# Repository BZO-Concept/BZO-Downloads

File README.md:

# BZO Concept – Downloads

Firmware, TunerStudio files, datasheets and tools for **BZO Concept** programmable ECUs and accessories.
This repository mirrors the *Téléchargements* section of [bzo-concept.fr](https://www.bzo-concept.fr/telechargements/).

Shop: [bzo-concept.fr/boutique](https://www.bzo-concept.fr/boutique/)

## ECUs (Speeduino based, STM32F4)

| Folder | Content |
|---|---|
| [Essential_v1.2](Essential_v1.2) | Firmware, TunerStudio `.ini`, base tune, datasheet |
| [Double_Eight](Double_Eight) | Firmware, TunerStudio `.ini`, base tune, datasheet (FR / EN) |
| [CoreF4_CoreF4_Boxed](CoreF4_CoreF4_Boxed) | Firmware packs `v1.2` and `2025.01.6`, `.ini`, base tunes, pinout, datasheet |
| [SmartBoard_v1.2](SmartBoard_v1.2) | Firmware (UART / USB) and integration kit: KiCad symbol, footprint, 3D model, pinout, typical application |

## Accessories

| Folder | Content |
|---|---|
| [PDU_v1.0](PDU_v1.0) | Power Distribution Unit – Arduino IDE source code, `.ini`, CAN frame sheet |
| [Mini_WideBand](Mini_WideBand) | Mini WideBand controller pinout |
| [DBW_Analog](DBW_Analog) | Analog drive-by-wire add-on datasheet |
| [Mini_OLED](Mini_OLED) | Multifunction mini OLED display datasheet |
| [Simulator](Simulator) | BZO engine simulator – source code, firmware, enclosure (FreeCAD / STEP) |
| [Bosch_55pin_Adapter](Bosch_55pin_Adapter) | Bosch 55-pin connector breakout plate (project originating from the rusEFI hardware repository) |
| [Bosch_88pin_Adapter](Bosch_88pin_Adapter) | Bosch 88-pin connector breakout plate – KiCad project and production files |
| [Speeduino_v0.4.3d](Speeduino_v0.4.3d) | BOM of the original Speeduino v0.4.3d board |

## Tools

- [BZO Programmer](Tools/BZO_Programmer) – Windows tool to flash BZO ECUs. Use it for every firmware update.
- STM32 drivers: [download from bzo-concept.fr](https://www.bzo-concept.fr/wp-content/uploads/2026/06/silent_st_drivers.zip)

## Documentation

- [Speeduino manual (EN)](https://www.bzo-concept.fr/wp-content/uploads/2025/11/Speeduino_manual.pdf)
- [Speeduino manual (FR)](https://www.bzo-concept.fr/wp-content/uploads/2025/11/Speeduino_manuel_en_fr.pdf)
- Official Speeduino project: [speeduino.com](https://speeduino.com) – [github.com/noisymime/speeduino](https://github.com/noisymime/speeduino)

## See also

Development boards and libraries: [BZO-Development](https://github.com/BZO-Concept/BZO-Development)

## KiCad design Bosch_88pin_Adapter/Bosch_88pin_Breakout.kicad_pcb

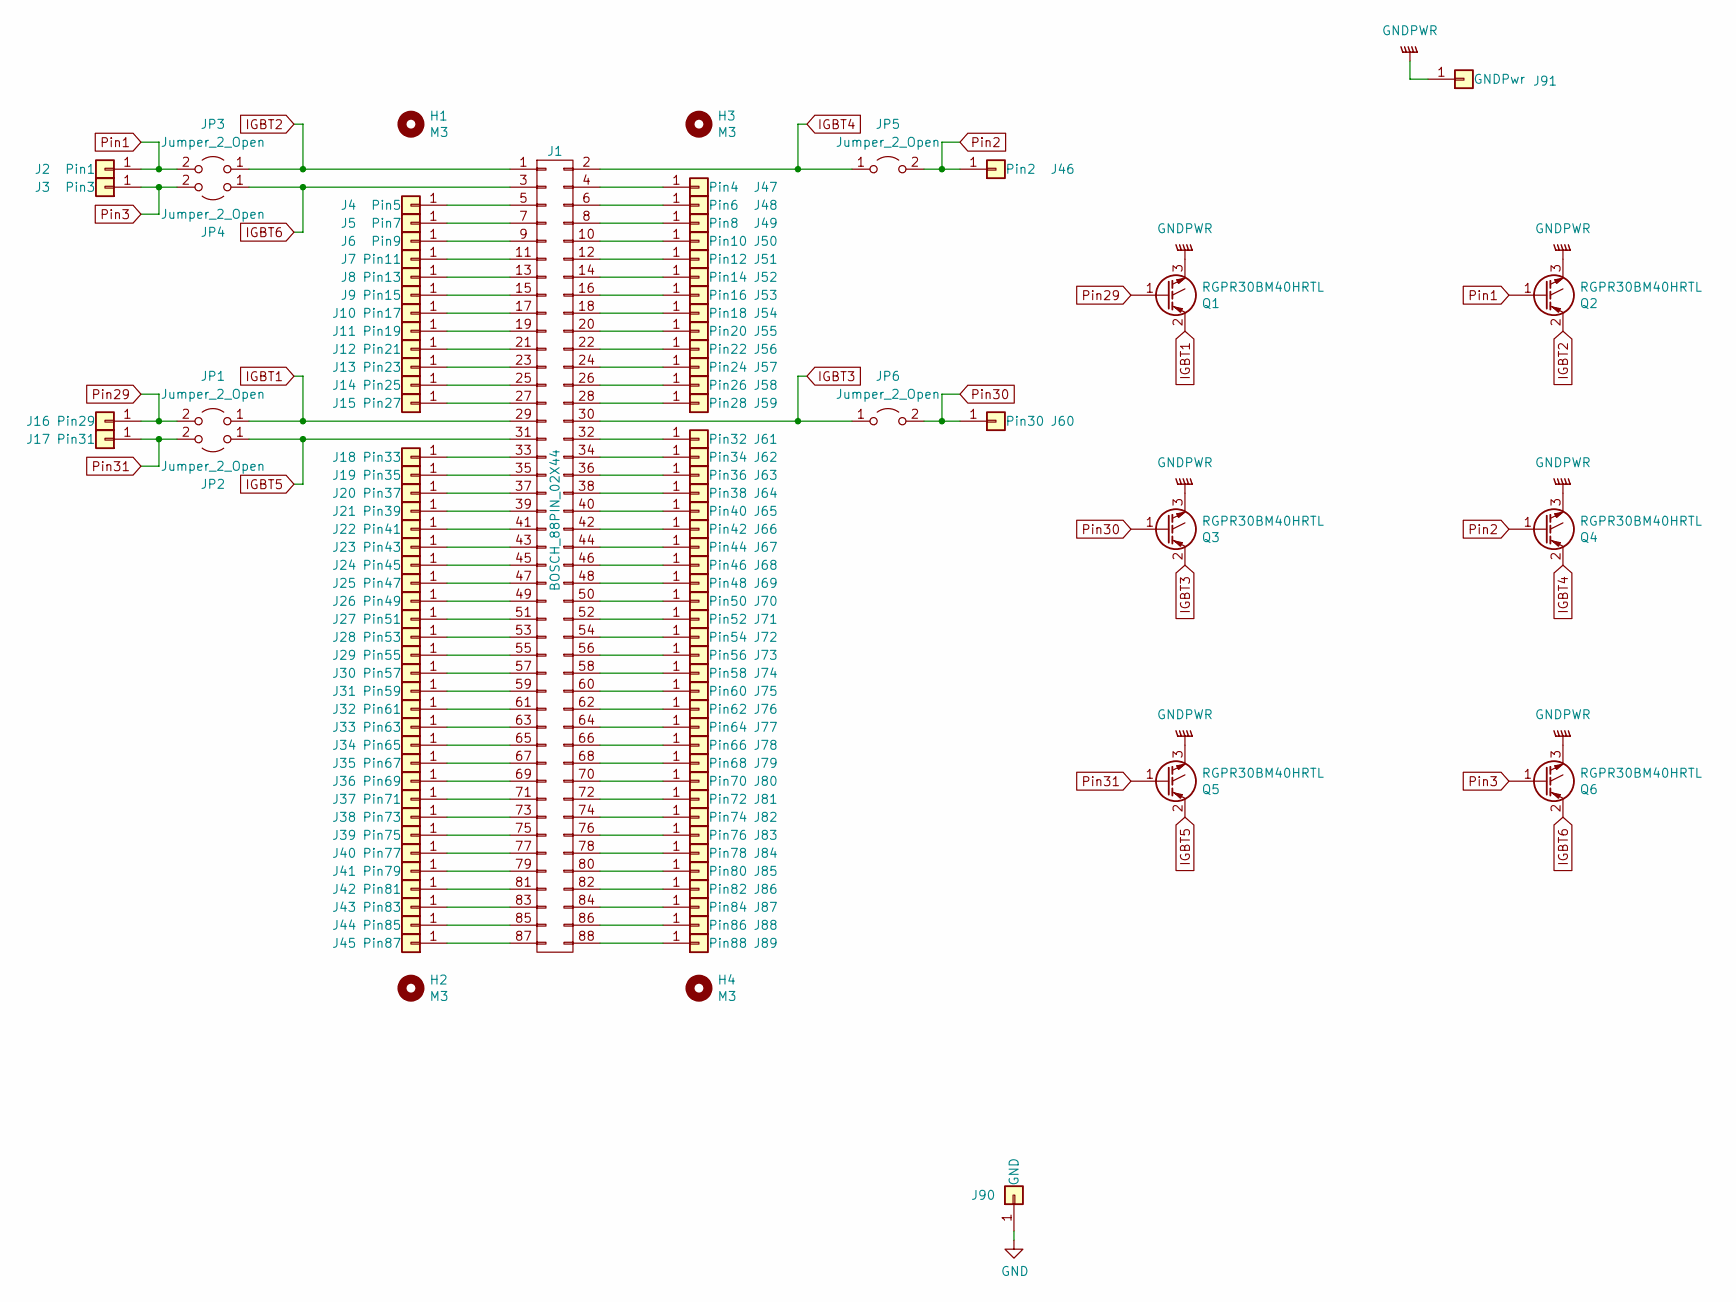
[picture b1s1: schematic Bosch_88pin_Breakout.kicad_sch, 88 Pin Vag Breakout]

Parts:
H1, H2, H3, H4: M3; MountingHole_3.2mm_M3_DIN965
J1: BOSCH_88PIN_02X44; BOSCH-88pin
J2: Pin1; TestPoint_Bridge_Pitch2.54mm_Drill1.3mm
J3: Pin3; TestPoint_Bridge_Pitch2.54mm_Drill1.3mm
J4: Pin5; TestPoint_Bridge_Pitch2.54mm_Drill1.3mm
J5: Pin7; TestPoint_Bridge_Pitch2.54mm_Drill1.3mm
J6: Pin9; TestPoint_Bridge_Pitch2.54mm_Drill1.3mm
J7: Pin11; TestPoint_Bridge_Pitch2.54mm_Drill1.3mm
J8: Pin13; TestPoint_Bridge_Pitch2.54mm_Drill1.3mm
J9: Pin15; TestPoint_Bridge_Pitch2.54mm_Drill1.3mm
J10: Pin17; TestPoint_Bridge_Pitch2.54mm_Drill1.3mm
J11: Pin19; TestPoint_Bridge_Pitch2.54mm_Drill1.3mm
J12: Pin21; TestPoint_Bridge_Pitch2.54mm_Drill1.3mm
J13: Pin23; TestPoint_Bridge_Pitch2.54mm_Drill1.3mm
J14: Pin25; TestPoint_Bridge_Pitch2.54mm_Drill1.3mm
J15: Pin27; TestPoint_Bridge_Pitch2.54mm_Drill1.3mm
J16: Pin29; TestPoint_Bridge_Pitch2.54mm_Drill1.3mm
J17: Pin31; TestPoint_Bridge_Pitch2.54mm_Drill1.3mm
J18: Pin33; TestPoint_Bridge_Pitch2.54mm_Drill1.3mm
J19: Pin35; TestPoint_Bridge_Pitch2.54mm_Drill1.3mm
J20: Pin37; TestPoint_Bridge_Pitch2.54mm_Drill1.3mm
J21: Pin39; TestPoint_Bridge_Pitch2.54mm_Drill1.3mm
J22: Pin41; TestPoint_Bridge_Pitch2.54mm_Drill1.3mm
J23: Pin43; TestPoint_Bridge_Pitch2.54mm_Drill1.3mm
J24: Pin45; TestPoint_Bridge_Pitch2.54mm_Drill1.3mm
J25: Pin47; TestPoint_Bridge_Pitch2.54mm_Drill1.3mm
J26: Pin49; TestPoint_Bridge_Pitch2.54mm_Drill1.3mm
J27: Pin51; TestPoint_Bridge_Pitch2.54mm_Drill1.3mm
J28: Pin53; TestPoint_Bridge_Pitch2.54mm_Drill1.3mm
J29: Pin55; TestPoint_Bridge_Pitch2.54mm_Drill1.3mm
J30: Pin57; TestPoint_Bridge_Pitch2.54mm_Drill1.3mm
J31: Pin59; TestPoint_Bridge_Pitch2.54mm_Drill1.3mm
J32: Pin61; TestPoint_Bridge_Pitch2.54mm_Drill1.3mm
J33: Pin63; TestPoint_Bridge_Pitch2.54mm_Drill1.3mm
J34: Pin65; TestPoint_Bridge_Pitch2.54mm_Drill1.3mm
J35: Pin67; TestPoint_Bridge_Pitch2.54mm_Drill1.3mm
J36: Pin69; TestPoint_Bridge_Pitch2.54mm_Drill1.3mm
J37: Pin71; TestPoint_Bridge_Pitch2.54mm_Drill1.3mm
J38: Pin73; TestPoint_Bridge_Pitch2.54mm_Drill1.3mm
J39: Pin75; TestPoint_Bridge_Pitch2.54mm_Drill1.3mm
J40: Pin77; TestPoint_Bridge_Pitch2.54mm_Drill1.3mm
J41: Pin79; TestPoint_Bridge_Pitch2.54mm_Drill1.3mm
J42: Pin81; TestPoint_Bridge_Pitch2.54mm_Drill1.3mm
J43: Pin83; TestPoint_Bridge_Pitch2.54mm_Drill1.3mm
J44: Pin85; TestPoint_Bridge_Pitch2.54mm_Drill1.3mm
J45: Pin87; TestPoint_Bridge_Pitch2.54mm_Drill1.3mm
J46: Pin2; TestPoint_Bridge_Pitch2.54mm_Drill1.3mm
J47: Pin4; TestPoint_Bridge_Pitch2.54mm_Drill1.3mm
J48: Pin6; TestPoint_Bridge_Pitch2.54mm_Drill1.3mm
J49: Pin8; TestPoint_Bridge_Pitch2.54mm_Drill1.3mm
J50: Pin10; TestPoint_Bridge_Pitch2.54mm_Drill1.3mm
J51: Pin12; TestPoint_Bridge_Pitch2.54mm_Drill1.3mm
J52: Pin14; TestPoint_Bridge_Pitch2.54mm_Drill1.3mm
J53: Pin16; TestPoint_Bridge_Pitch2.54mm_Drill1.3mm
J54: Pin18; TestPoint_Bridge_Pitch2.54mm_Drill1.3mm
J55: Pin20; TestPoint_Bridge_Pitch2.54mm_Drill1.3mm
J56: Pin22; TestPoint_Bridge_Pitch2.54mm_Drill1.3mm
J57: Pin24; TestPoint_Bridge_Pitch2.54mm_Drill1.3mm
J58: Pin26; TestPoint_Bridge_Pitch2.54mm_Drill1.3mm
J59: Pin28; TestPoint_Bridge_Pitch2.54mm_Drill1.3mm
J60: Pin30; TestPoint_Bridge_Pitch2.54mm_Drill1.3mm
J61: Pin32; TestPoint_Bridge_Pitch2.54mm_Drill1.3mm
J62: Pin34; TestPoint_Bridge_Pitch2.54mm_Drill1.3mm
J63: Pin36; TestPoint_Bridge_Pitch2.54mm_Drill1.3mm
J64: Pin38; TestPoint_Bridge_Pitch2.54mm_Drill1.3mm
J65: Pin40; TestPoint_Bridge_Pitch2.54mm_Drill1.3mm
J66: Pin42; TestPoint_Bridge_Pitch2.54mm_Drill1.3mm
J67: Pin44; TestPoint_Bridge_Pitch2.54mm_Drill1.3mm
J68: Pin46; TestPoint_Bridge_Pitch2.54mm_Drill1.3mm
J69: Pin48; TestPoint_Bridge_Pitch2.54mm_Drill1.3mm
J70: Pin50; TestPoint_Bridge_Pitch2.54mm_Drill1.3mm
J71: Pin52; TestPoint_Bridge_Pitch2.54mm_Drill1.3mm
J72: Pin54; TestPoint_Bridge_Pitch2.54mm_Drill1.3mm
J73: Pin56; TestPoint_Bridge_Pitch2.54mm_Drill1.3mm
J74: Pin58; TestPoint_Bridge_Pitch2.54mm_Drill1.3mm
J75: Pin60; TestPoint_Bridge_Pitch2.54mm_Drill1.3mm
J76: Pin62; TestPoint_Bridge_Pitch2.54mm_Drill1.3mm
J77: Pin64; TestPoint_Bridge_Pitch2.54mm_Drill1.3mm
J78: Pin66; TestPoint_Bridge_Pitch2.54mm_Drill1.3mm
J79: Pin68; TestPoint_Bridge_Pitch2.54mm_Drill1.3mm
J80: Pin70; TestPoint_Bridge_Pitch2.54mm_Drill1.3mm
J81: Pin72; TestPoint_Bridge_Pitch2.54mm_Drill1.3mm
J82: Pin74; TestPoint_Bridge_Pitch2.54mm_Drill1.3mm
J83: Pin76; TestPoint_Bridge_Pitch2.54mm_Drill1.3mm
J84: Pin78; TestPoint_Bridge_Pitch2.54mm_Drill1.3mm
J85: Pin80; TestPoint_Bridge_Pitch2.54mm_Drill1.3mm
J86: Pin82; TestPoint_Bridge_Pitch2.54mm_Drill1.3mm
J87: Pin84; TestPoint_Bridge_Pitch2.54mm_Drill1.3mm
J88: Pin86; TestPoint_Bridge_Pitch2.54mm_Drill1.3mm
J89: Pin88; TestPoint_Bridge_Pitch2.54mm_Drill1.3mm
J90: GND; TestPoint_Bridge_Pitch2.54mm_Drill1.3mm
J91: GNDPwr; TestPoint_Bridge_Pitch2.54mm_Drill1.3mm
JP1, JP2, JP3, JP4, JP5, JP6: Jumper_2_Open; SolderJumper-2_P1.3mm_Open_RoundedPad1.0x1.5mm
Q1, Q2, Q3, Q4, Q5, Q6: RGPR30BM40HRTL; TO-252-2; LCSC Part # RGPR30BM40HRTL

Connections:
GND: J90.1
GNDPWR: J91.1, Q1.3 (E), Q2.3 (E), Q3.3 (E), Q4.3 (E), Q5.3 (E), Q6.3 (E)
IGBT1: J1.29, JP1.1 (A), Q1.2 (C)
IGBT2: J1.1, JP3.1 (A), Q2.2 (C)
IGBT3: J1.30, JP6.1 (A), Q3.2 (C)
IGBT4: J1.2, JP5.1 (A), Q4.2 (C)
IGBT5: J1.31, JP2.1 (A), Q5.2 (C)
IGBT6: J1.3, JP4.1 (A), Q6.2 (C)
unnamed: J1.4, J47.1
unnamed: J1.5, J4.1
unnamed: J1.6, J48.1
unnamed: J1.7, J5.1
unnamed: J1.8, J49.1
unnamed: J1.9, J6.1
unnamed: J1.10, J50.1
unnamed: J1.11, J7.1
unnamed: J1.12, J51.1
unnamed: J1.13, J8.1
unnamed: J1.14, J52.1
unnamed: J1.15, J9.1
unnamed: J1.16, J53.1
unnamed: J1.17, J10.1
unnamed: J1.18, J54.1
unnamed: J1.19, J11.1
unnamed: J1.20, J55.1
unnamed: J1.21, J12.1
unnamed: J1.22, J56.1
unnamed: J1.23, J13.1
unnamed: J1.24, J57.1
unnamed: J1.25, J14.1
unnamed: J1.26, J58.1
unnamed: J1.27, J15.1
unnamed: J1.28, J59.1
unnamed: J1.32, J61.1
unnamed: J1.33, J18.1
unnamed: J1.34, J62.1
unnamed: J1.35, J19.1
unnamed: J1.36, J63.1
unnamed: J1.37, J20.1
unnamed: J1.38, J64.1
unnamed: J1.39, J21.1
unnamed: J1.40, J65.1
unnamed: J1.41, J22.1
unnamed: J1.42, J66.1
unnamed: J1.43, J23.1
unnamed: J1.44, J67.1
unnamed: J1.45, J24.1
unnamed: J1.46, J68.1
unnamed: J1.47, J25.1
unnamed: J1.48, J69.1
unnamed: J1.49, J26.1
unnamed: J1.50, J70.1
unnamed: J1.51, J27.1
unnamed: J1.52, J71.1
unnamed: J1.53, J28.1
unnamed: J1.54, J72.1
unnamed: J1.55, J29.1
unnamed: J1.56, J73.1
unnamed: J1.57, J30.1
unnamed: J1.58, J74.1
unnamed: J1.59, J31.1
unnamed: J1.60, J75.1
unnamed: J1.61, J32.1
unnamed: J1.62, J76.1
unnamed: J1.63, J33.1
unnamed: J1.64, J77.1
unnamed: J1.65, J34.1
unnamed: J1.66, J78.1
unnamed: J1.67, J35.1
unnamed: J1.68, J79.1
unnamed: J1.69, J36.1
unnamed: J1.70, J80.1
unnamed: J1.71, J37.1
unnamed: J1.72, J81.1
unnamed: J1.73, J38.1
unnamed: J1.74, J82.1
unnamed: J1.75, J39.1
unnamed: J1.76, J83.1
unnamed: J1.77, J40.1
unnamed: J1.78, J84.1
unnamed: J1.79, J41.1
unnamed: J1.80, J85.1
unnamed: J1.81, J42.1
unnamed: J1.83, J43.1
unnamed: J1.85, J44.1
unnamed: J1.87, J45.1
unnamed: J1.82, J86.1
unnamed: J1.84, J87.1
unnamed: J1.86, J88.1
unnamed: J1.88, J89.1
Pin1: J2.1, JP3.2 (B), Q2.1 (G)
Pin2: J46.1, JP5.2 (B), Q4.1 (G)
Pin3: J3.1, JP4.2 (B), Q6.1 (G)
Pin29: J16.1, JP1.2 (B), Q1.1 (G)
Pin30: J60.1, JP6.2 (B), Q3.1 (G)
Pin31: J17.1, JP2.2 (B), Q5.1 (G)

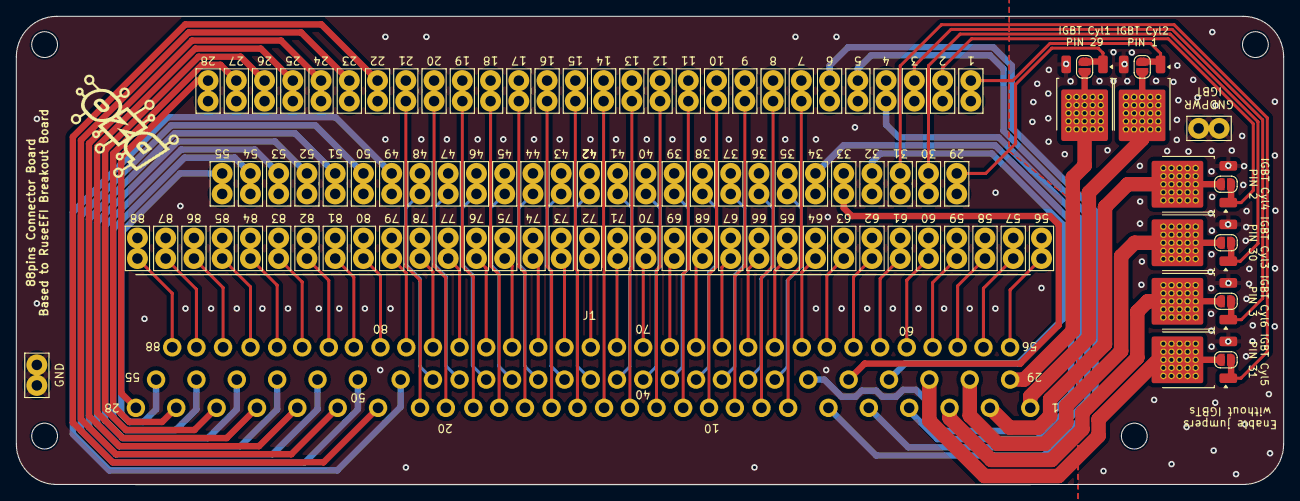
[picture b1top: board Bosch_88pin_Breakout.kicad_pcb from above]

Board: 2 copper layers, 157.0 x 58.0 mm, 108 parts (0 on the bottom side), 95 nets.

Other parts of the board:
G2: Disclaimer; Off_Road_Disclaimer
